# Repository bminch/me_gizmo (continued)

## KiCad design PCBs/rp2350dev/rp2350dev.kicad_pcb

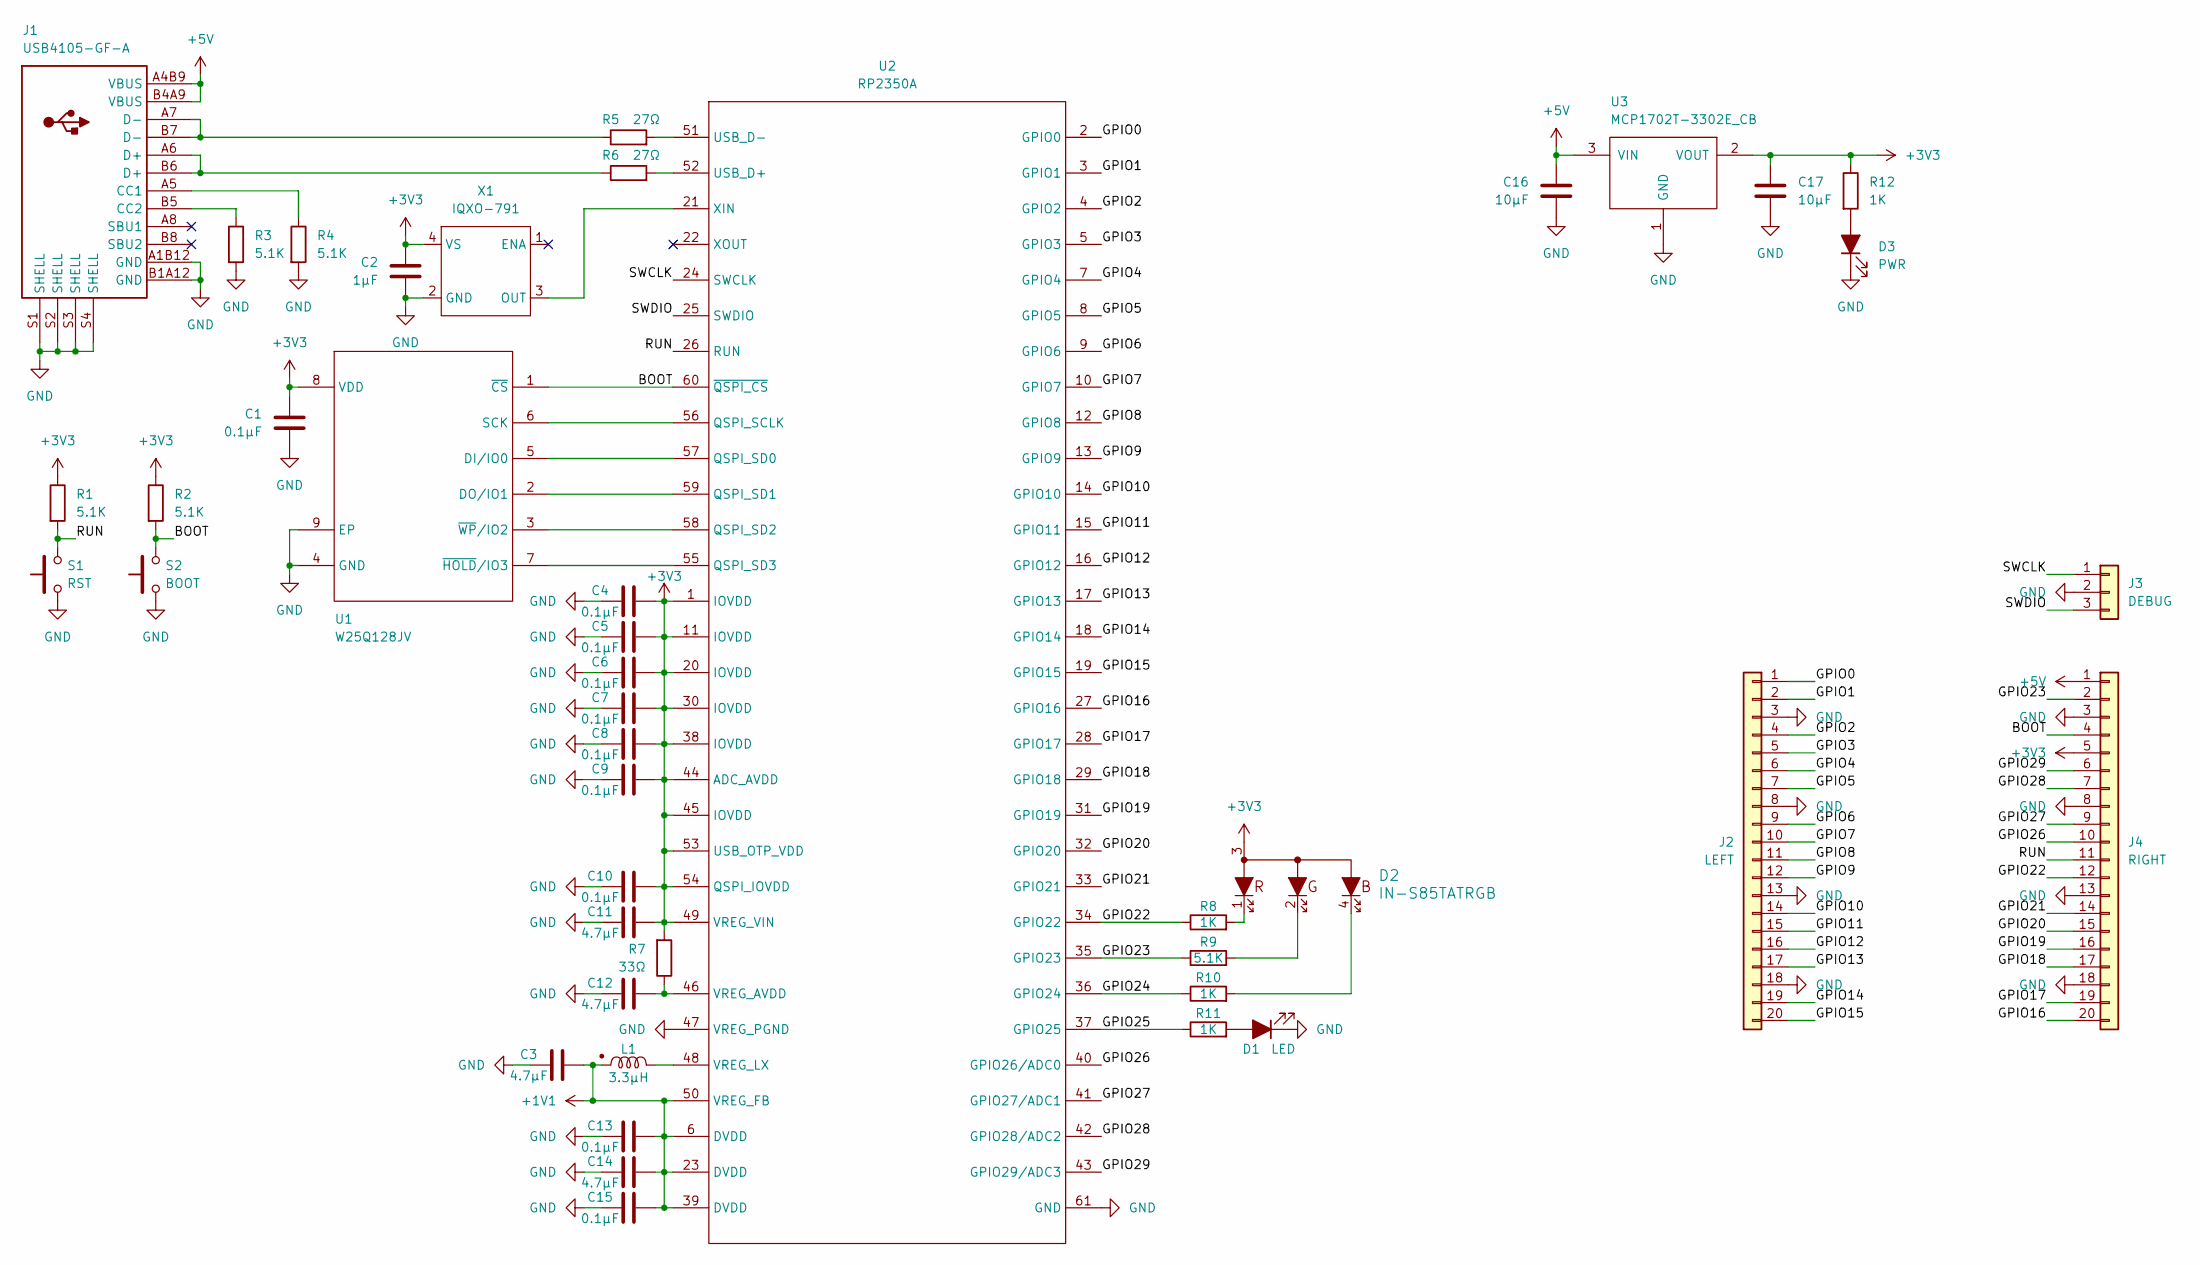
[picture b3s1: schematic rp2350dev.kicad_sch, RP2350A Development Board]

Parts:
C1, C4, C5, C6, C7, C8, C9, C10, C13, C15: 0.1µF; C_0402_1005Metric
C2: 1µF; C_0402_1005Metric
C3, C11, C12, C14: 4.7µF; C_0402_1005Metric
C16, C17: 10µF; C_0603_1608Metric
D1: LED; LED_0805_2012Metric
D2: IN-S85TATRGB
D3: PWR; LED_0805_2012Metric
J1: USB4105-GF-A
J2: LEFT; PinHeader_1x20_P2.54mm_Vertical
J3: DEBUG; PinHeader_1x03_P2.54mm_Vertical
J4: RIGHT; PinHeader_1x20_P2.54mm_Vertical
L1: 3.3µH; AOTA-B201610S3R3-101-T
R1, R2, R3, R4, R9: 5.1K; R_0402_1005Metric
R5, R6: 27Ω; R_0402_1005Metric
R7: 33Ω; R_0402_1005Metric
R8, R10, R11, R12: 1K; R_0402_1005Metric
S1: RST; SW_SPST_B3U-1000P
S2: BOOT; SW_SPST_B3U-1000P
U1: W25Q128JV; WSON-8-1EP_6x5mm_P1.27mm_EP3.4x4.3mm
U2: RP2350A; RP2350A_QFN-60_EP_7.75x7.75_Pitch0.4mm
U3: MCP1702T-3302E_CB; SOT-23
X1: IQXO-791

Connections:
+1V1: C3.2, C13.2, C14.2, C15.2, L1.1, U2.6 (DVDD), U2.23 (DVDD), U2.39 (DVDD), U2.50 (VREG_FB)
+3V3: C1.2, C2.2, C4.2, C5.2, C6.2, C7.2, C8.2, C9.2, C10.2, C11.2, C17.1, D2.3, J4.5, R1.1, R2.1, R7.2, R12.1, U1.8 (VDD), U2.1 (IOVDD), U2.11 (IOVDD), U2.20 (IOVDD), U2.30 (IOVDD), U2.38 (IOVDD), U2.44 (ADC_AVDD), U2.45 (IOVDD), U2.49 (VREG_VIN), U2.53 (USB_OTP_VDD), U2.54 (QSPI_IOVDD), U3.2 (VOUT), X1.4 (VS)
+5V: C16.2, J1.A4B9 (VBUS), J1.B4A9 (VBUS), J4.1, U3.3 (VIN)
/BOOT: J4.4, R2.2, S2.2, U1.1 (~CS), U2.60 (~QSPI_CS)
/GPIO0: J2.1, U2.2 (GPIO0)
/GPIO1: J2.2, U2.3 (GPIO1)
/GPIO2: J2.4, U2.4 (GPIO2)
/GPIO3: J2.5, U2.5 (GPIO3)
/GPIO4: J2.6, U2.7 (GPIO4)
/GPIO5: J2.7, U2.8 (GPIO5)
/GPIO6: J2.9, U2.9 (GPIO6)
/GPIO7: J2.10, U2.10 (GPIO7)
/GPIO8: J2.11, U2.12 (GPIO8)
/GPIO9: J2.12, U2.13 (GPIO9)
/GPIO10: J2.14, U2.14 (GPIO10)
/GPIO11: J2.15, U2.15 (GPIO11)
/GPIO12: J2.16, U2.16 (GPIO12)
/GPIO13: J2.17, U2.17 (GPIO13)
/GPIO14: J2.19, U2.18 (GPIO14)
/GPIO15: J2.20, U2.19 (GPIO15)
/GPIO16: J4.20, U2.27 (GPIO16)
/GPIO17: J4.19, U2.28 (GPIO17)
/GPIO18: J4.17, U2.29 (GPIO18)
/GPIO19: J4.16, U2.31 (GPIO19)
/GPIO20: J4.15, U2.32 (GPIO20)
/GPIO21: J4.14, U2.33 (GPIO21)
/GPIO22: J4.12, R8.1, U2.34 (GPIO22)
/GPIO23: J4.2, R9.1, U2.35 (GPIO23)
/GPIO24: R10.1, U2.36 (GPIO24)
/GPIO25: R11.1, U2.37 (GPIO25)
/GPIO26: J4.10, U2.40 (GPIO26/ADC0)
/GPIO27: J4.9, U2.41 (GPIO27/ADC1)
/GPIO28: J4.7, U2.42 (GPIO28/ADC2)
/GPIO29: J4.6, U2.43 (GPIO29/ADC3)
/RUN: J4.11, R1.2, S1.2, U2.26 (RUN)
/SWCLK: J3.1, U2.24 (SWCLK)
/SWDIO: J3.3, U2.25 (SWDIO)
GND: C1.1, C2.1, C3.1, C4.1, C5.1, C6.1, C7.1, C8.1, C9.1, C10.1, C11.1, C12.1, C13.1, C14.1, C15.1, C16.1, C17.2, D1.1 (K), D3.1 (K), J1.A1B12 (GND), J1.B1A12 (GND), J1.S1 (SHELL), J1.S2 (SHELL), J1.S3 (SHELL), J1.S4 (SHELL), J2.3, J2.8, J2.13, J2.18, J3.2, J4.3, J4.8, J4.13, J4.18, R3.2, R4.2, S1.1, S2.1, U1.4 (GND), U1.9 (EP), U2.47 (VREG_PGND), U2.61 (GND), U3.1 (GND), X1.2 (GND)
unnamed: D1.2 (A), R11.2
unnamed: D2.1, R8.2
unnamed: D2.2, R9.2
unnamed: D2.4, R10.2
unnamed: D3.2 (A), R12.2
unnamed: J1.A5 (CC1), R4.1
unnamed: J1.B5 (CC2), R3.1
unnamed: J1.A6 (D+), J1.B6 (D+), R6.1
unnamed: J1.A7 (D-), J1.B7 (D-), R5.1
unnamed: U1.5 (DI/IO0), U2.57 (QSPI_SD0)
unnamed: U1.2 (DO/IO1), U2.59 (QSPI_SD1)
unnamed: U1.6 (SCK), U2.56 (QSPI_SCLK)
unnamed: U1.7 (~HOLD/IO3), U2.55 (QSPI_SD3)
unnamed: U1.3 (~WP/IO2), U2.58 (QSPI_SD2)
unnamed: R6.2, U2.52 (USB_D+)
unnamed: R5.2, U2.51 (USB_D-)
unnamed: C12.2, R7.1, U2.46 (VREG_AVDD)
unnamed: L1.2, U2.48 (VREG_LX)
unnamed: U2.21 (XIN), X1.3 (OUT)

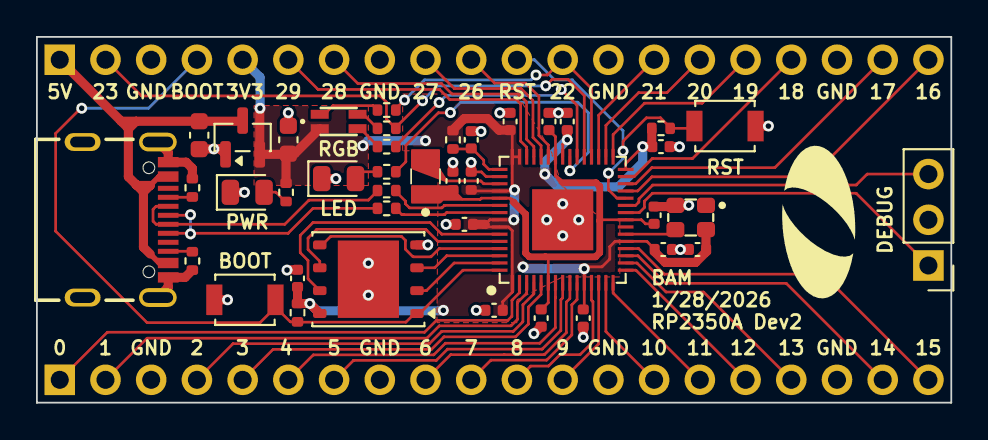
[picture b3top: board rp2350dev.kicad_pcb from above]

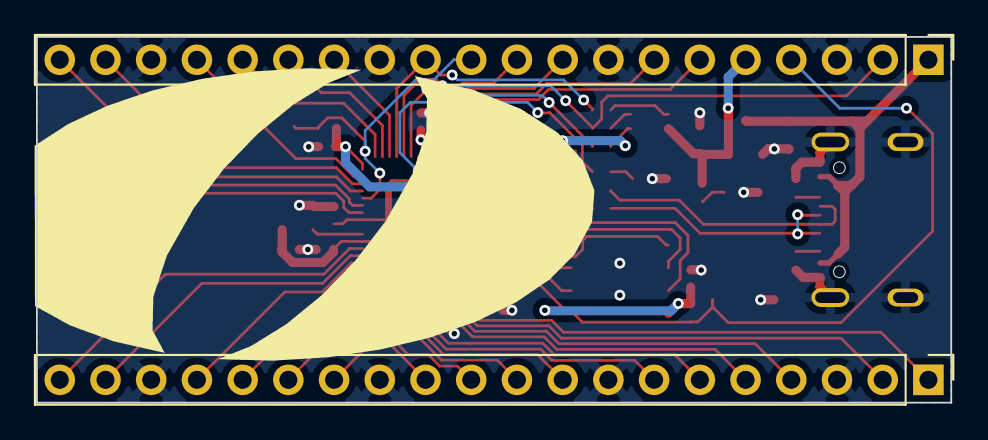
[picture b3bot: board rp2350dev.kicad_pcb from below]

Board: 2 copper layers, 50.8 x 20.3 mm, 45 parts (3 on the bottom side), 57 nets.

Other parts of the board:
OlinLogoLg1: G***; OlinLogoLg1
OlinLogoTruncated_0.6in: G***; OlinLogoTruncated_0.6in

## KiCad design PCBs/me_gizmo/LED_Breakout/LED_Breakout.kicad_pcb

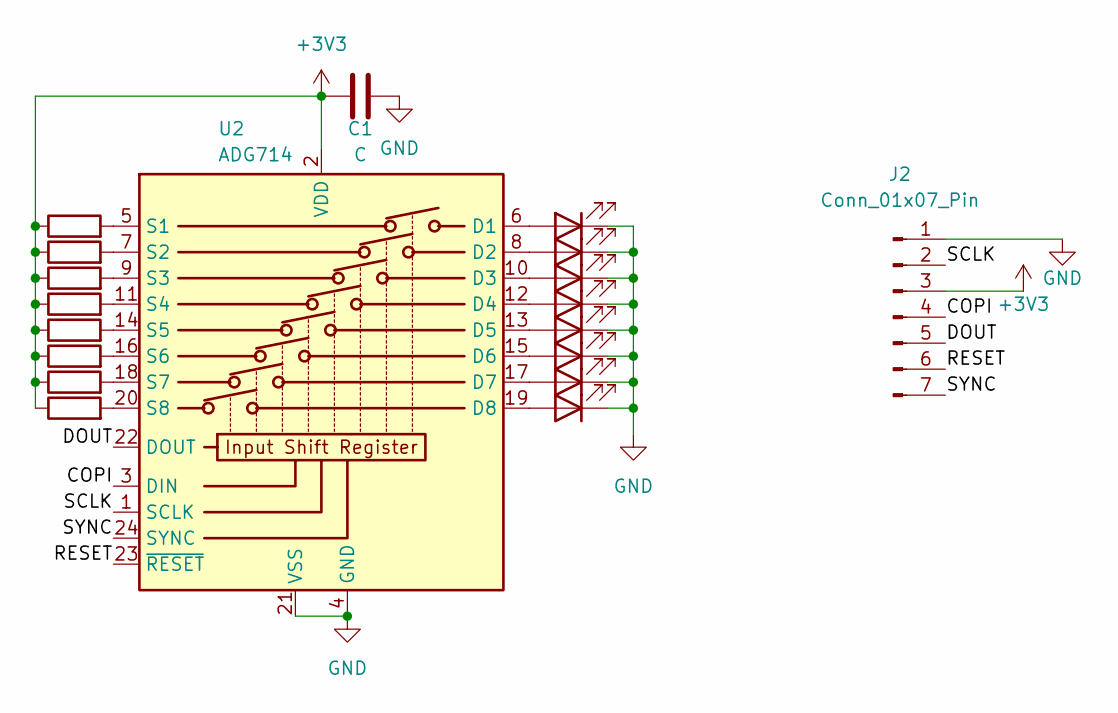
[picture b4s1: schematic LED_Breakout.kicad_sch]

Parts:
C1: C; C_0603_1608Metric
D1, D2, D3, D4, D5, D6, D7, D8: LED; D_0603_1608Metric
J2: Conn_01x07_Pin; PinHeader_1x07_P2.54mm_Vertical
R1, R2, R3, R4, R5, R6, R7, R8: R; R_0603_1608Metric
U2: ADG714; TSSOP-24_4.4x7.8mm_P0.65mm

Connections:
+3V3: C1.1, J2.3, R1.1, R2.1, R3.1, R4.1, R5.1, R6.1, R7.1, R8.1, U2.2 (VDD)
/COPI: J2.4, U2.3 (DIN)
/DOUT: J2.5, U2.22 (DOUT)
/RESET: J2.6, U2.23 (~RESET)
/SCLK: J2.2, U2.1 (SCLK)
/SYNC: J2.7, U2.24 (SYNC)
GND: C1.2, D1.1 (K), D2.1 (K), D3.1 (K), D4.1 (K), D5.1 (K), D6.1 (K), D7.1 (K), D8.1 (K), J2.1, U2.4 (GND), U2.21 (VSS)
unnamed: D1.2 (A), U2.12 (D4)
unnamed: D2.2 (A), U2.10 (D3)
unnamed: D3.2 (A), U2.8 (D2)
unnamed: D4.2 (A), U2.6 (D1)
unnamed: D5.2 (A), U2.19 (D8)
unnamed: D6.2 (A), U2.17 (D7)
unnamed: D7.2 (A), U2.15 (D6)
unnamed: D8.2 (A), U2.13 (D5)
unnamed: R1.2, U2.5 (S1)
unnamed: R2.2, U2.7 (S2)
unnamed: R3.2, U2.9 (S3)
unnamed: R4.2, U2.11 (S4)
unnamed: R5.2, U2.14 (S5)
unnamed: R6.2, U2.16 (S6)
unnamed: R7.2, U2.18 (S7)
unnamed: R8.2, U2.20 (S8)

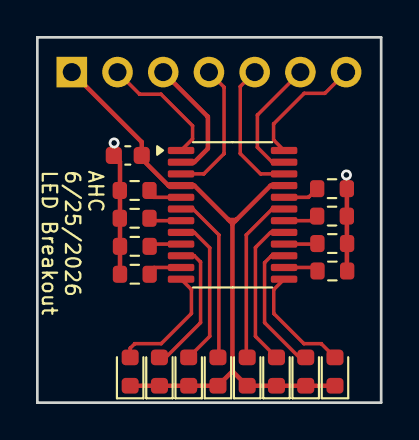
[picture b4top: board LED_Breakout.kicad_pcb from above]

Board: 2 copper layers, 19.1 x 20.3 mm, 19 parts (1 on the bottom side), 23 nets.

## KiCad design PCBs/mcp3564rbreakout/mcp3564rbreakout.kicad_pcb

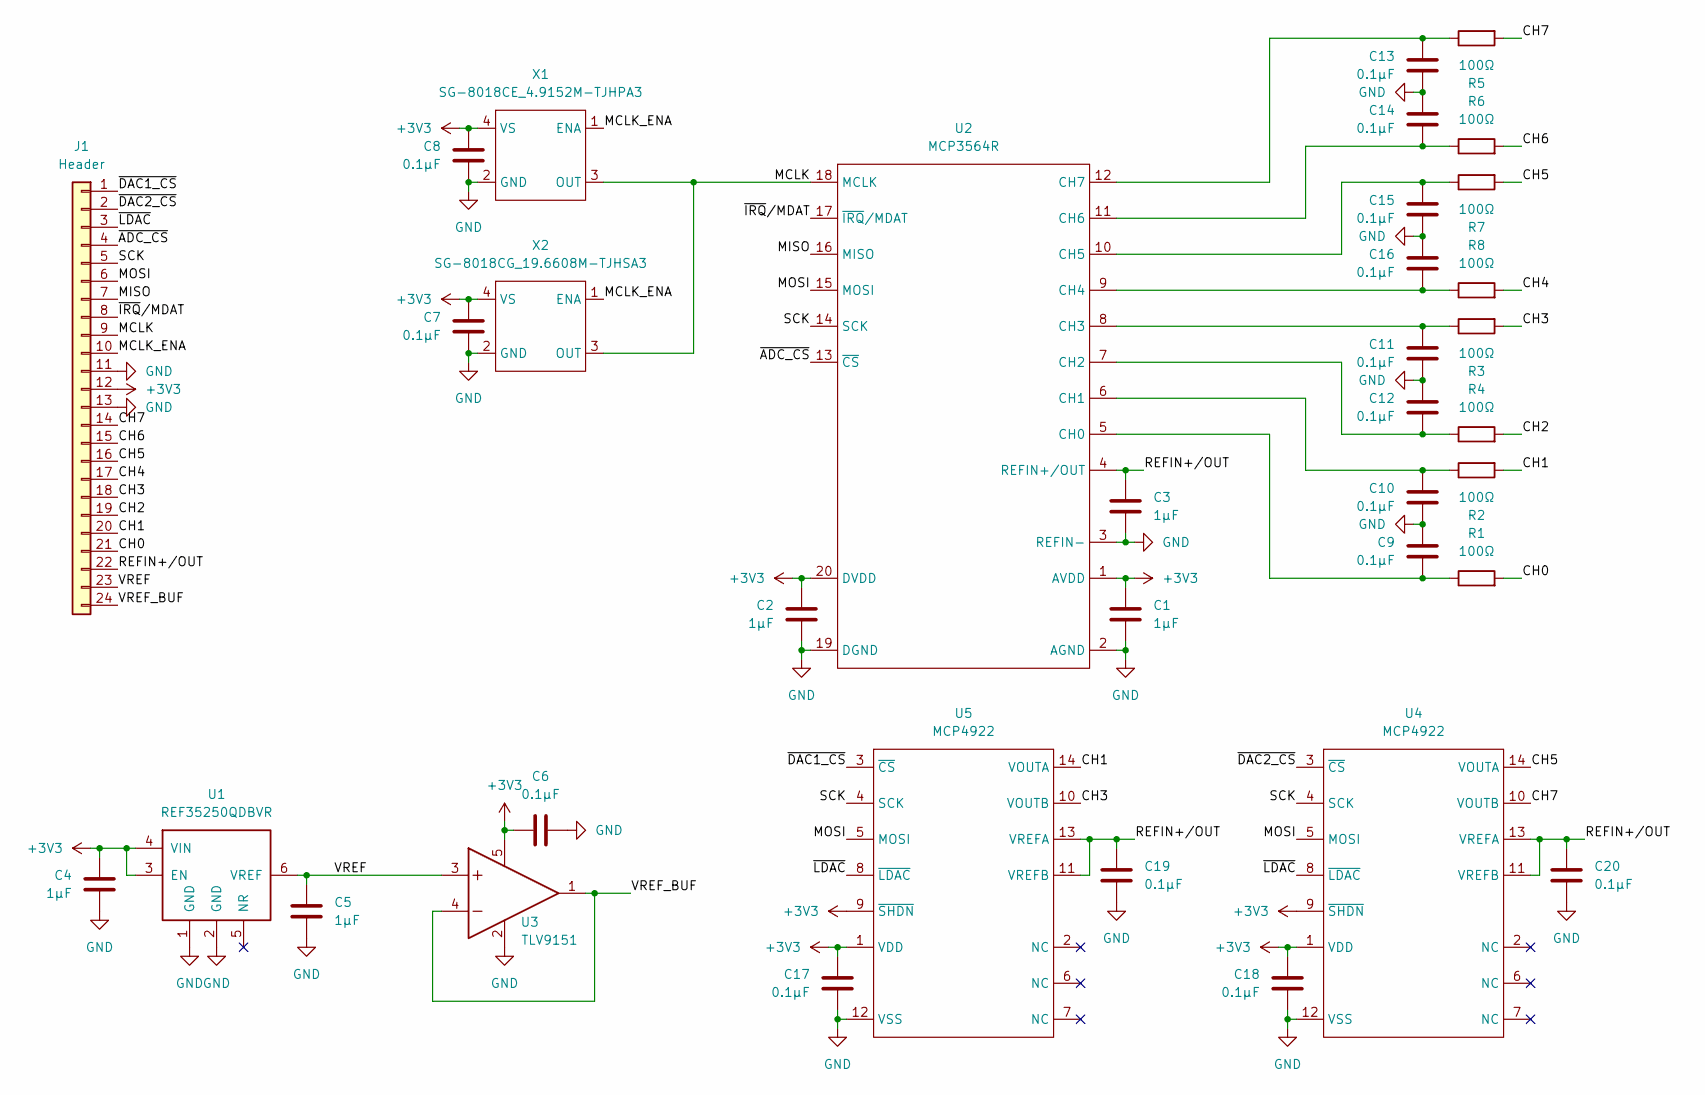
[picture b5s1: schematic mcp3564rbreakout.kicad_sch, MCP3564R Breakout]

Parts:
C1, C2, C3, C4, C5: 1µF; C_0603_1608Metric
C6, C7, C8, C9, C10, C11, C12, C13, C14, C15, C16, C17, C18, C19, C20: 0.1µF; C_0603_1608Metric
J1: Header; PinHeader_1x24_P2.54mm_Vertical
R1, R2, R3, R4, R5, R6, R7, R8: 100Ω; R_0603_1608Metric
U1: REF35250QDBVR; SOT-23-6
U2: MCP3564R; TSSOP-20_4.4x6.5mm_P0.65mm
U3: TLV9151; SOT-23-5
U4, U5: MCP4922; TSSOP-14_4.4x5mm_P0.65mm
X1: SG-8018CE_4.9152M-TJHPA3; Crystal_SMD_3225-4Pin_3.2x2.5mm
X2: SG-8018CG_19.6608M-TJHSA3; Crystal_SMD_2520-4Pin_2.5x2.0mm

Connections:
+3V3: C1.1, C2.1, C4.1, C6.1, C7.1, C8.1, C17.1, C18.1, J1.12, U1.3 (EN), U1.4 (VIN), U2.1 (AVDD), U2.20 (DVDD), U3.5, U4.1 (VDD), U4.9 (~SHDN), U5.1 (VDD), U5.9 (~SHDN), X1.4 (VS), X2.4 (VS)
/CH0: J1.21, R1.2
/CH1: J1.20, R2.2, U5.14 (VOUTA)
/CH2: J1.19, R4.2
/CH3: J1.18, R3.2, U5.10 (VOUTB)
/CH4: J1.17, R8.2
/CH5: J1.16, R7.2, U4.14 (VOUTA)
/CH6: J1.15, R6.2
/CH7: J1.14, R5.2, U4.10 (VOUTB)
/MCLK: J1.9, U2.18 (MCLK), X1.3 (OUT), X2.3 (OUT)
/MCLK_ENA: J1.10, X1.1 (ENA), X2.1 (ENA)
/MISO: J1.7, U2.16 (MISO)
/MOSI: J1.6, U2.15 (MOSI), U4.5 (MOSI), U5.5 (MOSI)
/REFIN+/OUT: C3.1, C19.1, C20.1, J1.22, U2.4 (REFIN+/OUT), U4.11 (VREFB), U4.13 (VREFA), U5.11 (VREFB), U5.13 (VREFA)
/SCK: J1.5, U2.14 (SCK), U4.4 (SCK), U5.4 (SCK)
/VREF: C5.1, J1.23, U1.6 (VREF), U3.3
/VREF_BUF: J1.24, U3.1, U3.4
/~ADC_CS: J1.4, U2.13 (~CS)
/~DAC1_CS: J1.1, U5.3 (~CS)
/~DAC2_CS: J1.2, U4.3 (~CS)
/~IRQ/MDAT: J1.8, U2.17 (~IRQ/MDAT)
/~LDAC: J1.3, U4.8 (~LDAC), U5.8 (~LDAC)
GND: C1.2, C2.2, C3.2, C4.2, C5.2, C6.2, C7.2, C8.2, C9.1, C10.2, C11.2, C12.1, C13.2, C14.1, C15.2, C16.1, C17.2, C18.2, C19.2, C20.2, J1.11, J1.13, U1.1 (GND), U1.2 (GND), U2.2 (AGND), U2.3 (REFIN-), U2.19 (DGND), U3.2, U4.12 (VSS), U5.12 (VSS), X1.2 (GND), X2.2 (GND)
unnamed: C9.2, R1.1, U2.5 (CH0)
unnamed: C10.1, R2.1, U2.6 (CH1)
unnamed: C12.2, R4.1, U2.7 (CH2)
unnamed: C11.1, R3.1, U2.8 (CH3)
unnamed: C16.2, R8.1, U2.9 (CH4)
unnamed: C15.1, R7.1, U2.10 (CH5)
unnamed: C14.2, R6.1, U2.11 (CH6)
unnamed: C13.1, R5.1, U2.12 (CH7)

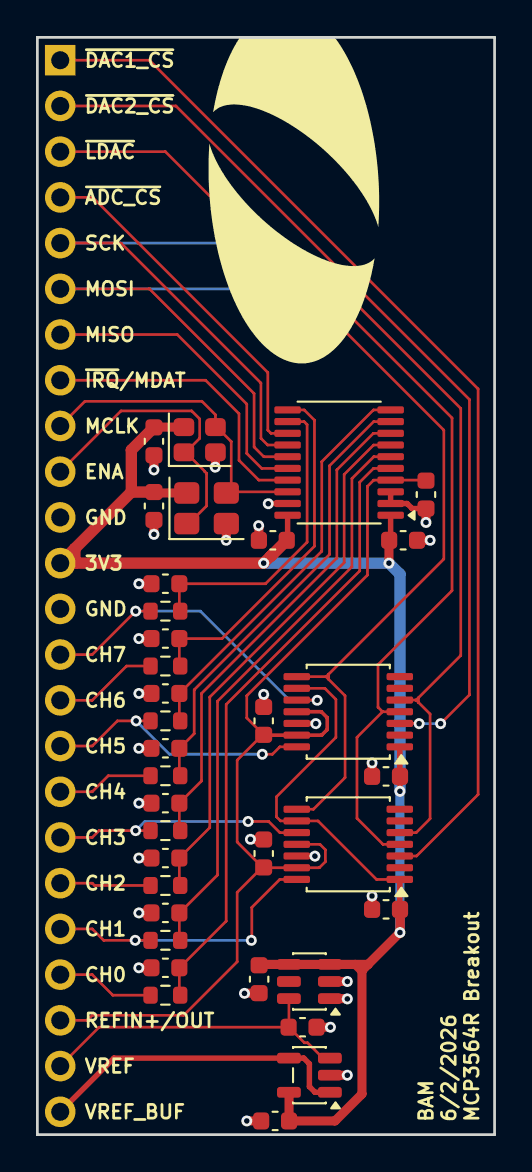
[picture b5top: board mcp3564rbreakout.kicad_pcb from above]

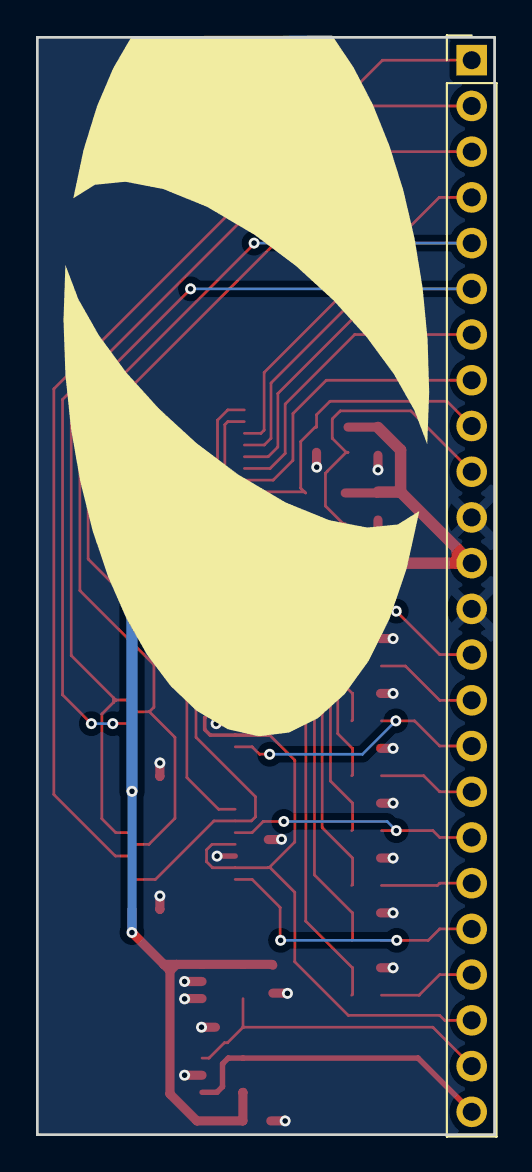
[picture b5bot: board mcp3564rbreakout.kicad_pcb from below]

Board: 2 copper layers, 25.4 x 61.0 mm, 38 parts (2 on the bottom side), 31 nets.

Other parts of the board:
OlinLogoTruncated: G***; OlinLogoTruncated
svg2mod: G***; OlinLogoTruncated_0.35in

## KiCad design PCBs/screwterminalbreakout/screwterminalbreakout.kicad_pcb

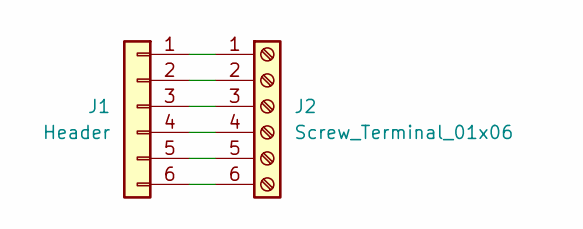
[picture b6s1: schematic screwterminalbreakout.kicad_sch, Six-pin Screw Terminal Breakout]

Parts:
J1: Header; PinHeader_1x06_P2.54mm_Vertical
J2: Screw_Terminal_01x06; TerminalBlock_Phoenix_MPT-0,5-6-2.54_1x06_P2.54mm_Horizontal

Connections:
unnamed: J1.1, J2.1
unnamed: J1.2, J2.2
unnamed: J1.3, J2.3
unnamed: J1.4, J2.4
unnamed: J1.5, J2.5
unnamed: J1.6, J2.6

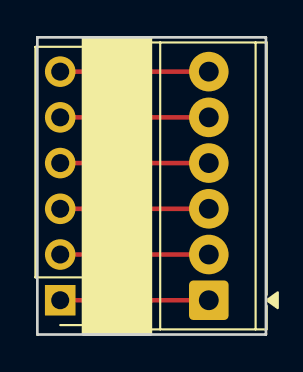
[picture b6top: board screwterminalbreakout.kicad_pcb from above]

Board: 2 copper layers, 12.7 x 16.5 mm, 3 parts (1 on the bottom side), 6 nets.

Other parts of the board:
svg2mod: G***; OlinLogoTruncated_0.225in

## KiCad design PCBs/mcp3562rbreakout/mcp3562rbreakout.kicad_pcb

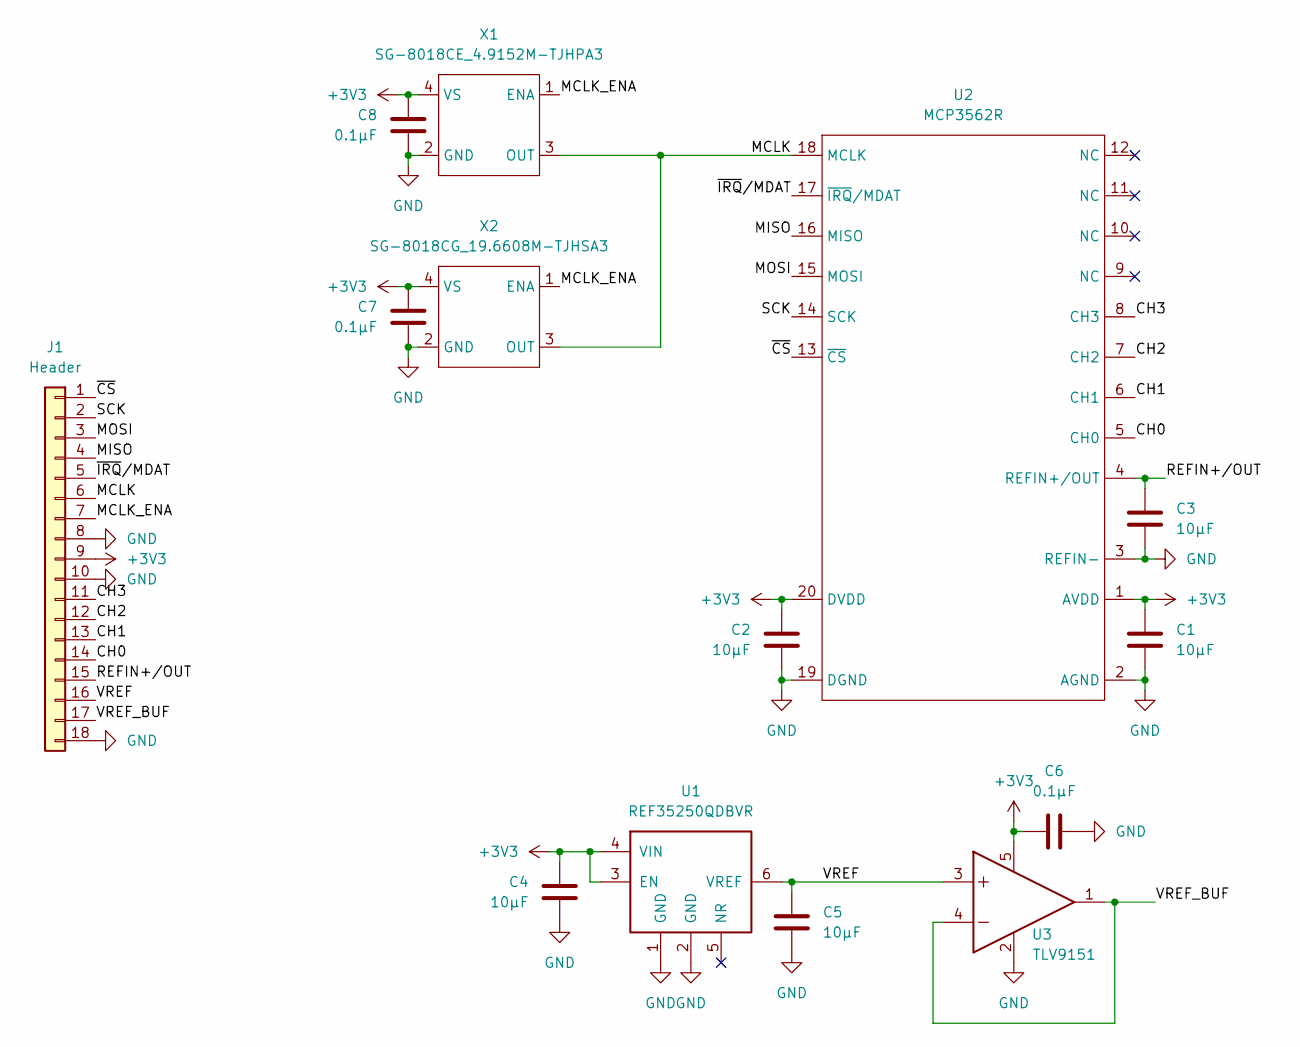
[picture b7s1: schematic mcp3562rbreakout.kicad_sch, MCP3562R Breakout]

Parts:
C1, C2, C3, C4, C5: 10µF; C_0603_1608Metric
C6, C7, C8: 0.1µF; C_0603_1608Metric
J1: Header; PinHeader_1x18_P2.54mm_Vertical
U1: REF35250QDBVR; SOT-23-6
U2: MCP3562R; TSSOP-20_4.4x6.5mm_P0.65mm
U3: TLV9151; SOT-23-5
X1: SG-8018CE_4.9152M-TJHPA3; Crystal_SMD_3225-4Pin_3.2x2.5mm
X2: SG-8018CG_19.6608M-TJHSA3; Crystal_SMD_2520-4Pin_2.5x2.0mm

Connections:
+3V3: C1.1, C2.1, C4.1, C6.1, C7.1, C8.1, J1.9, U1.3 (EN), U1.4 (VIN), U2.1 (AVDD), U2.20 (DVDD), U3.5, X1.4 (VS), X2.4 (VS)
/CH0: J1.14, U2.5 (CH0)
/CH1: J1.13, U2.6 (CH1)
/CH2: J1.12, U2.7 (CH2)
/CH3: J1.11, U2.8 (CH3)
/MCLK: J1.6, U2.18 (MCLK), X1.3 (OUT), X2.3 (OUT)
/MCLK_ENA: J1.7, X1.1 (ENA), X2.1 (ENA)
/MISO: J1.4, U2.16 (MISO)
/MOSI: J1.3, U2.15 (MOSI)
/REFIN+/OUT: C3.1, J1.15, U2.4 (REFIN+/OUT)
/SCK: J1.2, U2.14 (SCK)
/VREF: C5.1, J1.16, U1.6 (VREF), U3.3
/VREF_BUF: J1.17, U3.1, U3.4
/~CS: J1.1, U2.13 (~CS)
/~IRQ/MDAT: J1.5, U2.17 (~IRQ/MDAT)
GND: C1.2, C2.2, C3.2, C4.2, C5.2, C6.2, C7.2, C8.2, J1.8, J1.10, J1.18, U1.1 (GND), U1.2 (GND), U2.2 (AGND), U2.3 (REFIN-), U2.19 (DGND), U3.2, X1.2 (GND), X2.2 (GND)

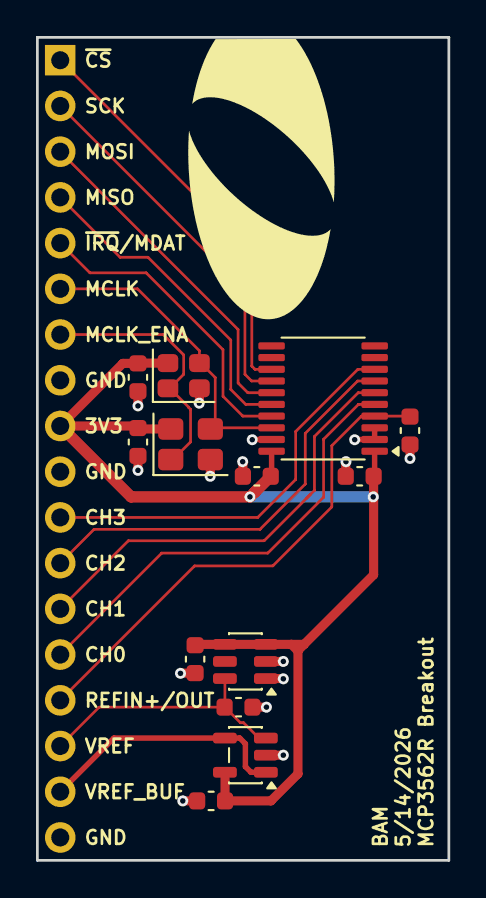
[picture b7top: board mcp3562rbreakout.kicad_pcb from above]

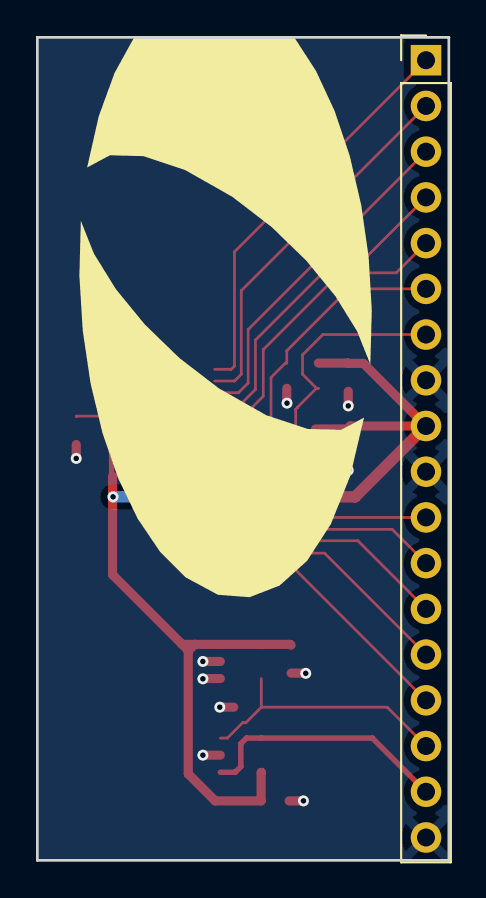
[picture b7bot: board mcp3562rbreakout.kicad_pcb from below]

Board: 2 copper layers, 22.9 x 45.7 mm, 16 parts (2 on the bottom side), 16 nets.

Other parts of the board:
OlinLogoTruncated_0.6in: G***; OlinLogoTruncated_0.6in
svg2mod: G***; OlinLogoTruncated_0.3in

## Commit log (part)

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2026-06-04 Created KiCAD conceptual schematic for strain gauge connections
2026-06-11 Added MCP3564R breakout board and added supporting firmware / software.
2026-06-15 Fixed bug in calibrate.py where MUX register had been set to MUX_DIFFCD rather than MUX_DIFFAB.
2026-06-15 Collection script that utilizes the streaming feature for 4-channel ADC and kicad schematic for wheatstone bridge breakout board
2026-06-23 Fixing abad merge
2026-06-23 Completed ADG714 Breakout kicad (awaiting further review)
2026-06-24 Updated resistor values in schematic, moved vias off pads, added bypass capacitors
2026-06-25 Added a BOM for the WB breakout and made a LED indicator breakout board
2026-06-26 Fixed pin header width in WB breakout
2026-06-29 Added rp2350dev PCB design files.
2026-06-29 Added rp2350dev_rainbow sample Arduino project.
